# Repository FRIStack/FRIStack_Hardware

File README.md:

# FRI_STACK

Modular stackable embedded system based on ESP32 microcontrollers

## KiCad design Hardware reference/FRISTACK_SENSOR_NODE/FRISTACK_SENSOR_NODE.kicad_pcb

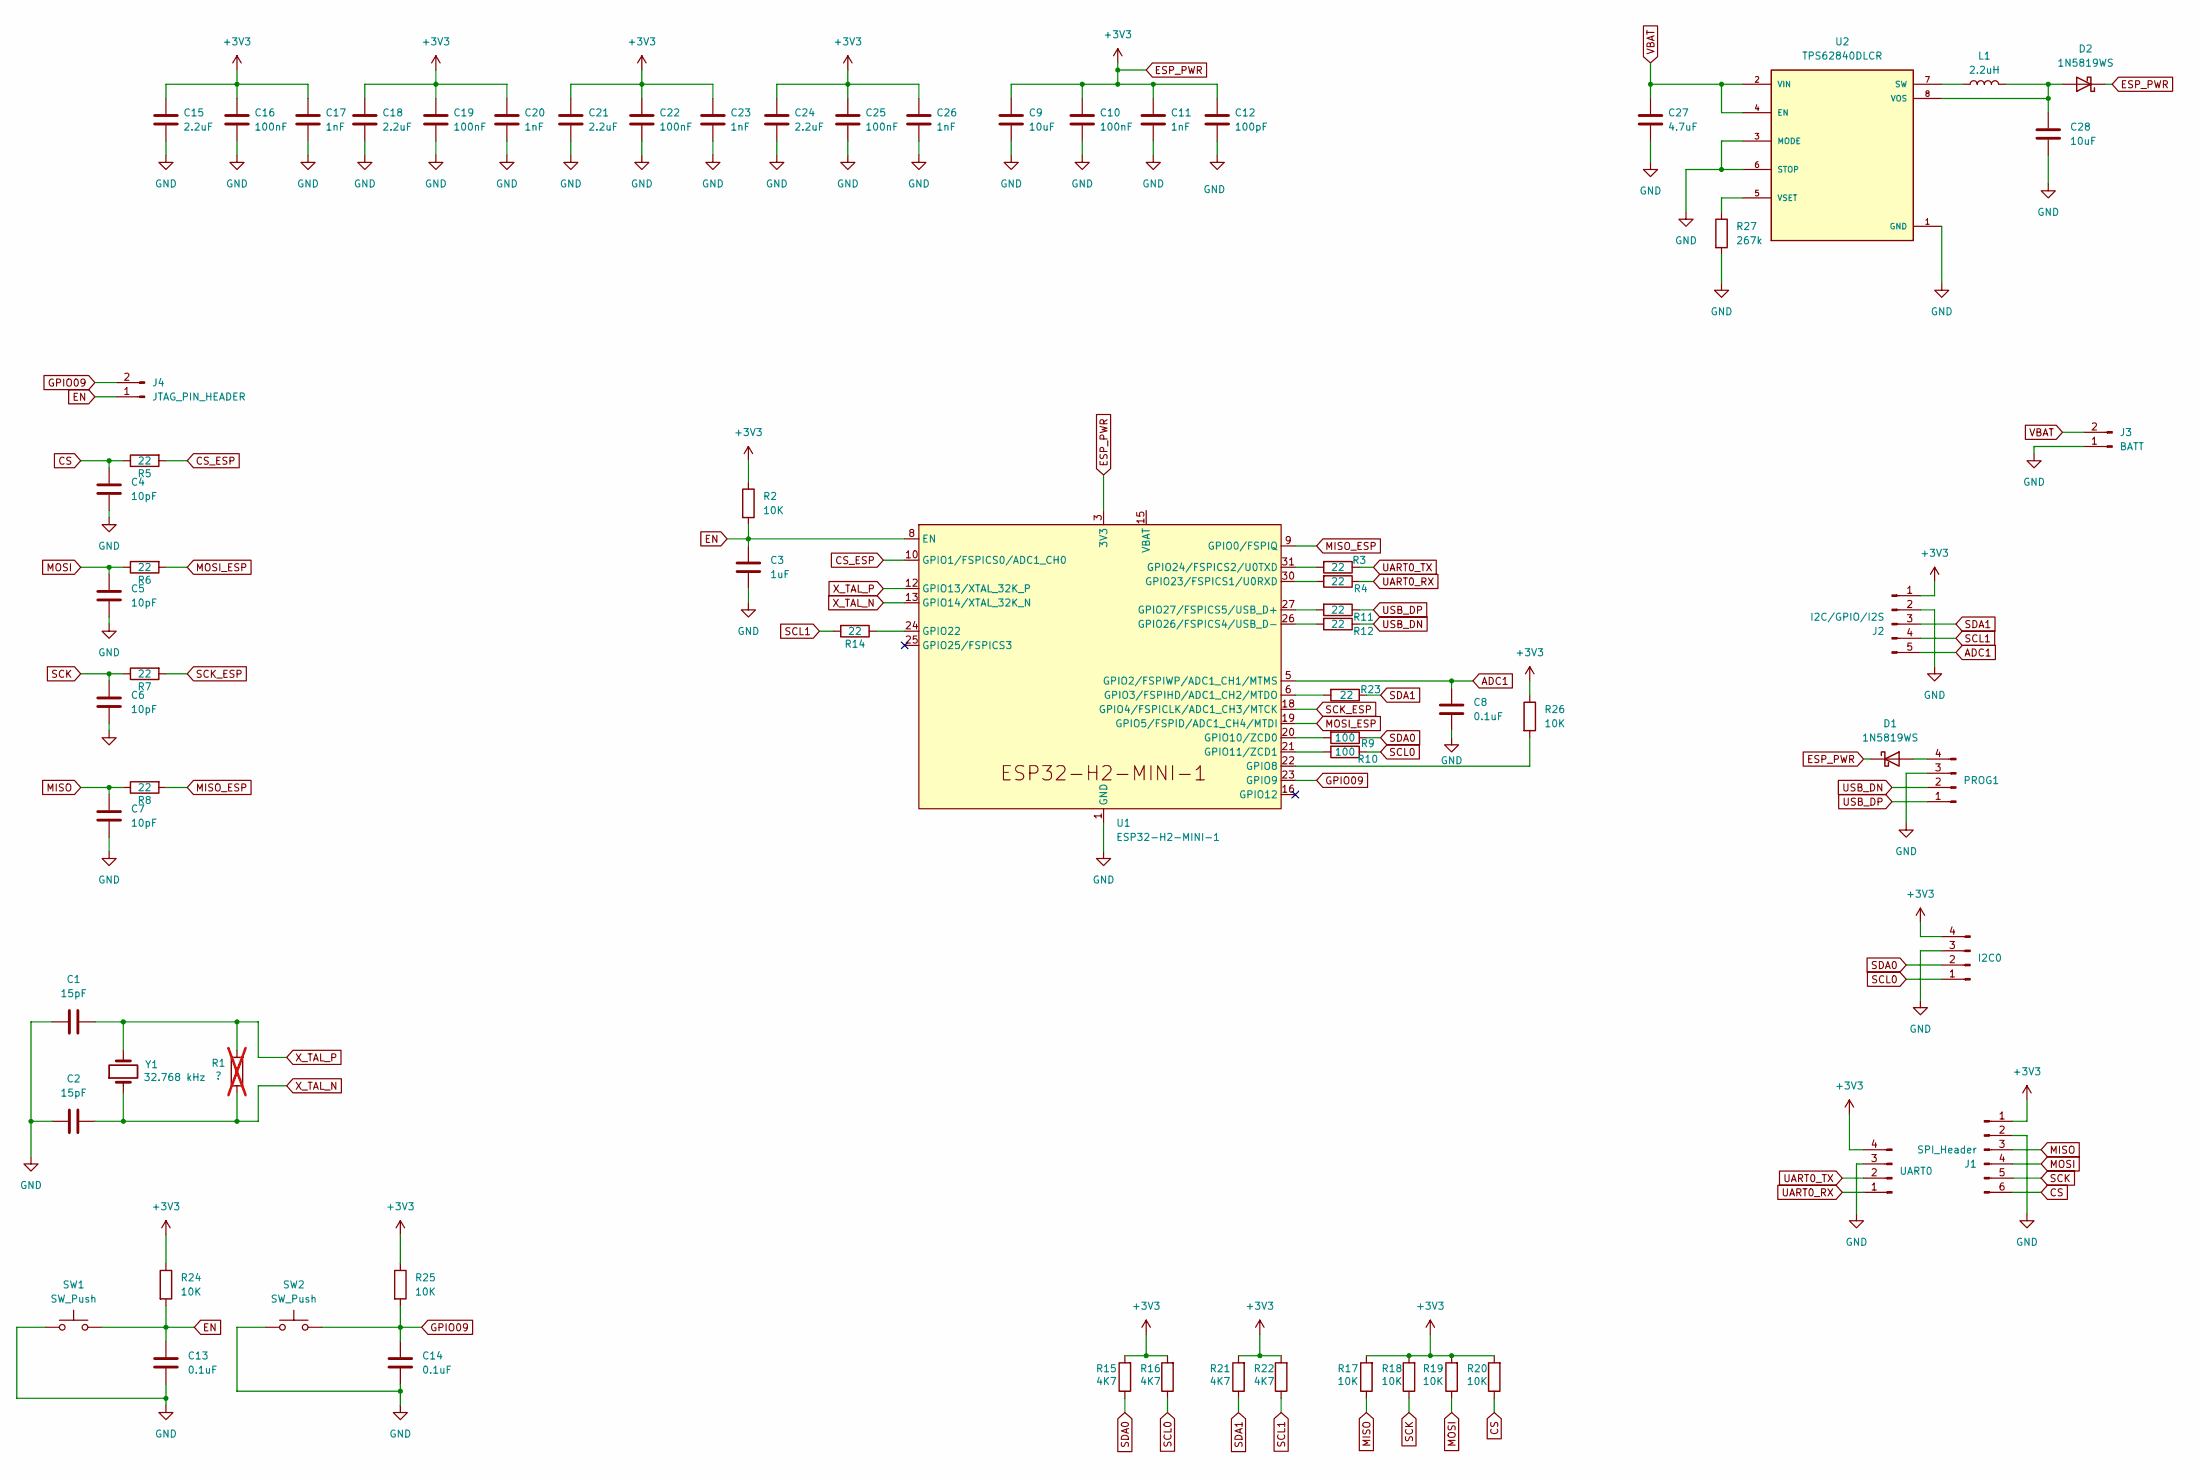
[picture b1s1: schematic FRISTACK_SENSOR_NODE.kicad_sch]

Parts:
C1, C2: 15pF; C_0603_1608Metric
C3: 1uF; C_0603_1608Metric
C4, C5, C6, C7: 10pF; C_0603_1608Metric
C8, C13, C14: 0.1uF; C_0603_1608Metric
C9: 10uF; C_0603_1608Metric
C10, C16, C19, C22, C25: 100nF; C_0603_1608Metric
C11, C17, C20, C23, C26: 1nF; C_0603_1608Metric
C12: 100pF; C_0603_1608Metric
C15, C18, C21, C24: 2.2uF; C_0603_1608Metric
C27: 4.7uF; C_0402_1005Metric
C28: 10uF; C_0402_1005Metric
D1, D2: 1N5819WS; D_SOD-323
I2C0: Conn_01x04_Pin; JST_PH_S4B-PH-K_1x04_P2.00mm_Horizontal
J1: SPI_Header; JST_PH_S6B-PH-K_1x06_P2.00mm_Horizontal
J2: I2C/GPIO/I2S; JST_PH_S5B-PH-K_1x05_P2.00mm_Horizontal
J3: BATT; JST_PH_S2B-PH-K_1x02_P2.00mm_Horizontal
J4: JTAG_PIN_HEADER; PinHeader_1x02_P2.54mm_Horizontal
L1: 2.2uH; INDC2016X120N
PROG1: Conn_01x04_Pin; JST_PH_S4B-PH-K_1x04_P2.00mm_Horizontal
R1: ?; R_0603_1608Metric; not fitted
R2, R17, R18, R19, R20, R24, R25, R26: 10K; R_0603_1608Metric
R3, R4, R5, R6, R7, R8, R11, R12, R14, R23: 22; R_0603_1608Metric
R9, R10: 100; R_0603_1608Metric
R15, R16, R21, R22: 4K7; R_0603_1608Metric
R27: 267k; R_0603_1608Metric
SW1, SW2: SW_Push; SW_TS-1088-AR02016
U1: ESP32-H2-MINI-1
U2: TPS62840DLCR; SON50P200X150X100-8N
UART0: Conn_01x04_Pin; JST_PH_S4B-PH-K_1x04_P2.00mm_Horizontal
Y1: 32.768 kHz; Crystal_SMD_G8-2Pin_3.2x1.5mm

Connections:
ADC1: C8.1, J2.5, U1.5 (GPIO2/FSPIWP/ADC1_CH1/MTMS)
CS: C4.1, J1.6, R5.1, R20.1
CS_ESP: R5.2, U1.10 (GPIO1/FSPICS0/ADC1_CH0)
EN: C3.1, C13.1, J4.1, R2.2, R24.2, SW1.2, U1.8 (EN); also elsewhere on the board
ESP_PWR: C9.1, C10.1, C11.1, C12.1, C15.1, C16.1, C17.1, C18.1, C19.1, C20.1, C21.1, C22.1, C23.1, C24.1, C25.1, C26.1, D1.1 (K), D2.1 (K), I2C0.4, J1.1, J2.1, R2.1, R15.2, R16.2, R17.2, R18.2, R19.2, R20.2, R21.2, R22.2, R24.1, R25.1, R26.1, U1.3 (3V3), UART0.4
GND: C1.1, C2.1, C3.2, C4.2, C5.2, C6.2, C7.2, C8.2, C9.2, C10.2, C11.2, C12.2, C13.2, C14.2, C15.2, C16.2, C17.2, C18.2, C19.2, C20.2, C21.2, C22.2, C23.2, C24.2, C25.2, C26.2, C27.2, C28.2, I2C0.3, J1.2, J2.2, J3.1, PROG1.3, R27.2, SW1.1, SW2.1, U1.1 (GND), U1.2 (GND), U1.11 (GND), U1.14 (GND), U1.36 (GND), U1.37 (GND), U1.38 (GND), U1.39 (GND), U1.40 (GND), U1.41 (GND), U1.42 (GND), U1.43 (GND), U1.44 (GND), U1.45 (GND), U1.46 (GND), U1.47 (GND), U1.48 (GND), U1.49 (GND), U1.50 (GND), U1.51 (GND), U1.52 (GND), U1.53 (GND), U2.1 (GND), U2.3 (MODE), U2.6 (STOP), UART0.3; also elsewhere on the board
GPIO09: C14.1, J4.2, R25.2, SW2.2, U1.23 (GPIO9); also elsewhere on the board
MISO: C7.1, J1.3, R8.1, R17.1
MISO_ESP: R8.2, U1.9 (GPIO0/FSPIQ)
MOSI: C5.1, J1.4, R6.1, R19.1
MOSI_ESP: R6.2, U1.19 (GPIO5/FSPID/ADC1_CH4/MTDI)
unnamed: D1.2 (A), PROG1.4
unnamed: C28.1, D2.2 (A), L1.2, U2.8 (VOS)
unnamed: R23.2, U1.6 (GPIO3/FSPIHD/ADC1_CH2/MTDO)
unnamed: R26.2, U1.22 (GPIO8)
unnamed: R9.2, U1.20 (GPIO10/ZCD0)
unnamed: R10.2, U1.21 (GPIO11/ZCD1)
unnamed: R14.1, U1.24 (GPIO22)
unnamed: R4.2, U1.30 (GPIO23/FSPICS1/U0RXD)
unnamed: R3.2, U1.31 (GPIO24/FSPICS2/U0TXD)
unnamed: R12.2, U1.26 (GPIO26/FSPICS4/USB_D-)
unnamed: R11.2, U1.27 (GPIO27/FSPICS5/USB_D+)
unnamed: L1.1, U2.7 (SW)
unnamed: R27.1, U2.5 (VSET)
SCK: C6.1, J1.5, R7.1, R18.1
SCK_ESP: R7.2, U1.18 (GPIO4/FSPICLK/ADC1_CH3/MTCK)
SCL0: I2C0.1, R10.1, R16.1
SCL1: J2.4, R14.2, R22.1
SDA0: I2C0.2, R9.1, R15.1
SDA1: J2.3, R21.1, R23.1
UART0_RX: R4.1, UART0.1
UART0_TX: R3.1, UART0.2
USB_DN: PROG1.2, R12.1
USB_DP: PROG1.1, R11.1
VBAT: C27.1, J3.2, U2.2 (VIN), U2.4 (EN)
X_TAL_N: C2.2, R1.1, U1.13 (GPIO14/XTAL_32K_N), Y1.1
X_TAL_P: C1.2, R1.2, U1.12 (GPIO13/XTAL_32K_P), Y1.2

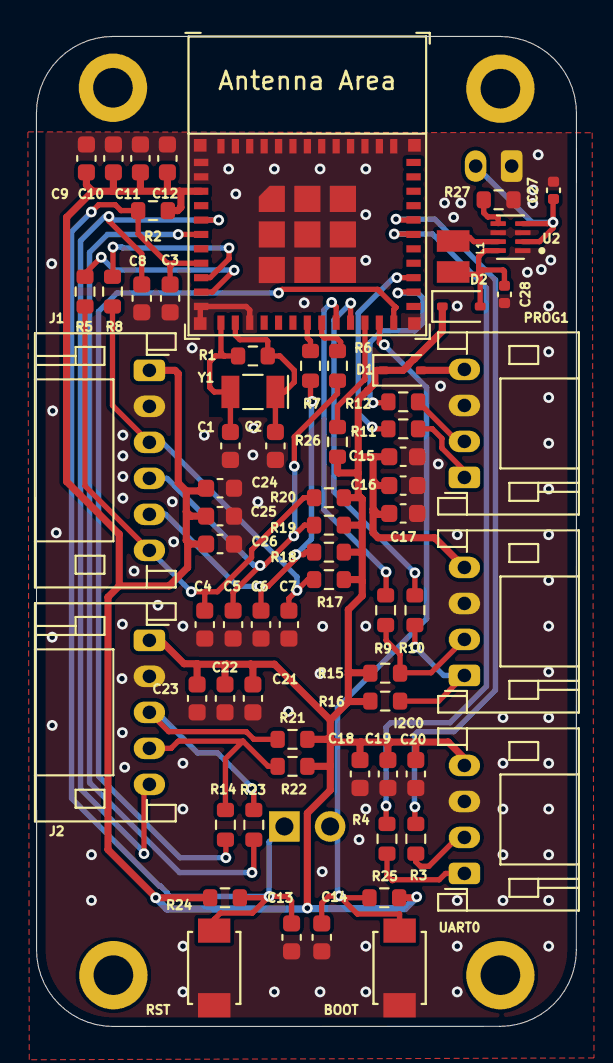
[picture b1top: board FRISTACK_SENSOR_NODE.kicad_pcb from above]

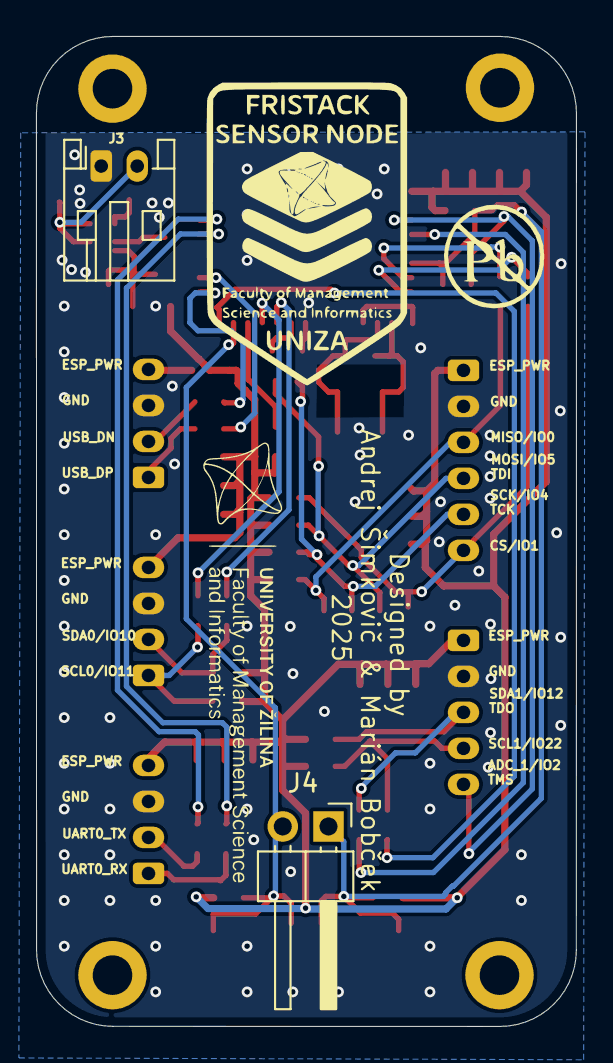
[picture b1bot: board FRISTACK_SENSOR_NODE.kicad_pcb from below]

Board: 2 copper layers, 30.0 x 55.0 mm, 69 parts (2 on the bottom side), 37 nets.

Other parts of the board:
BOOT: SW_Push; SW_TS-1088-AR02016
RST: SW_Push; SW_TS-1088-AR02016

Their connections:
EN: RST.2; also elsewhere on the board
GND: BOOT.1, RST.1; also elsewhere on the board
GPIO09: BOOT.2; also elsewhere on the board

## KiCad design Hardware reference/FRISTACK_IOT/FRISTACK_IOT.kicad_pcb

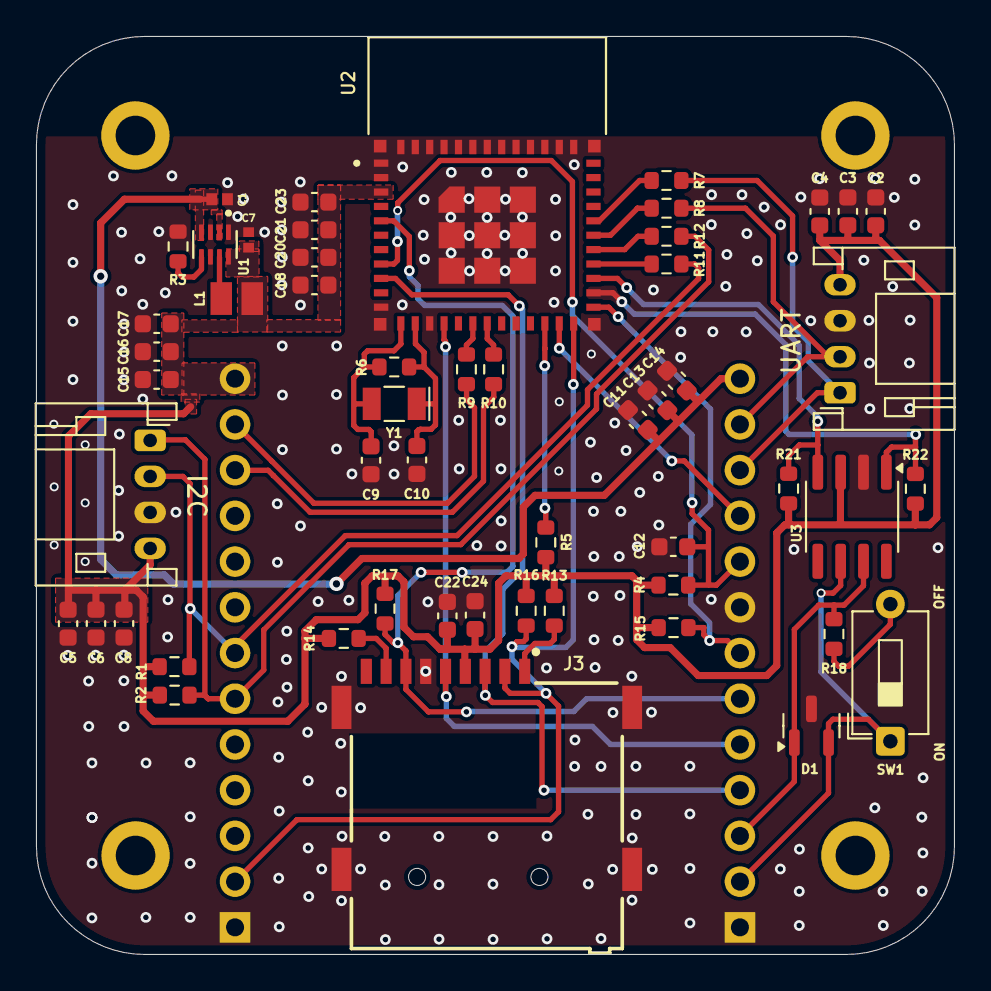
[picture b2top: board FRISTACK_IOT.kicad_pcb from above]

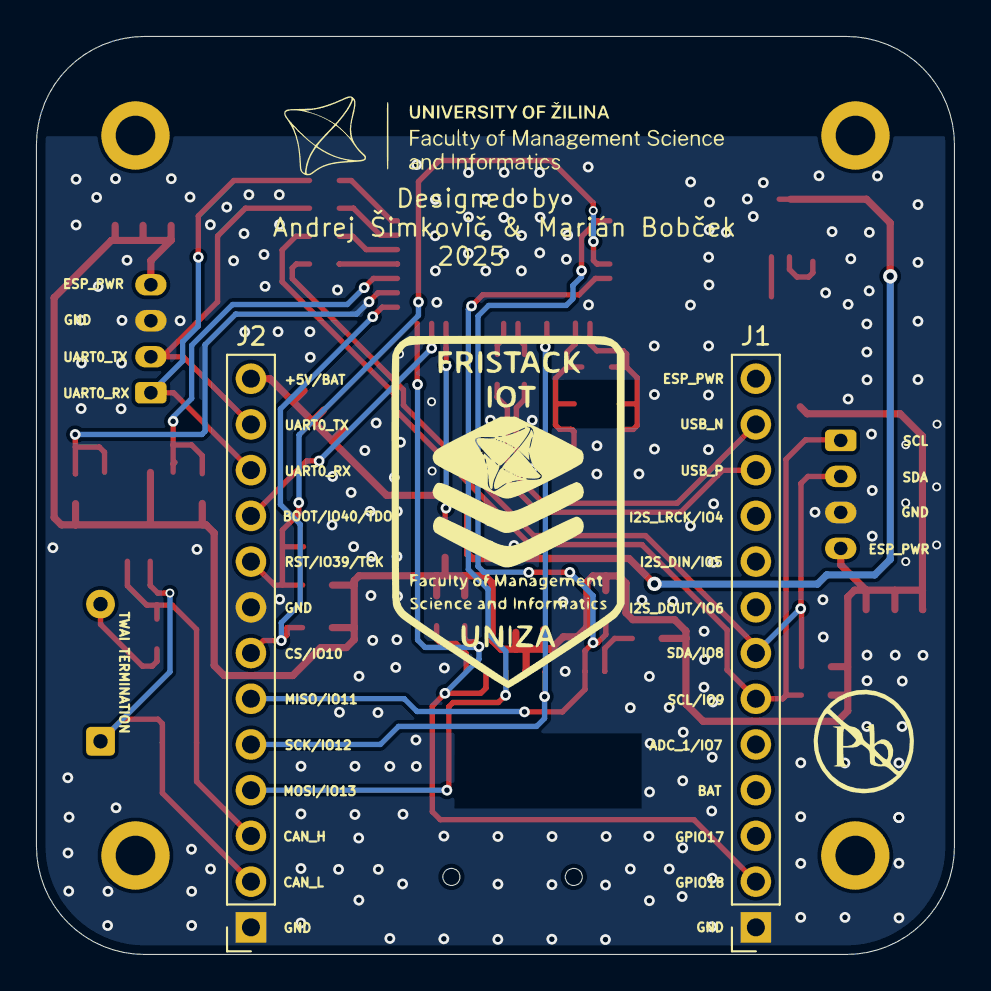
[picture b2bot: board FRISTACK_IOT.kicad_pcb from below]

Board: 2 copper layers, 51.0 x 51.0 mm, 55 parts (2 on the bottom side), 34 nets.

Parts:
C1: 4.7uF; CAPC1005X65N
C2, C5, C11, C15: 2.2uF; C_0603_1608Metric
C3, C6, C13, C16, C20, C24: 100nF; C_0603_1608Metric
C4, C8, C14, C17, C21: 1nF; C_0603_1608Metric
C7: 10uF; CAPC1005X55N
C9, C10: 15pF; C_0603_1608Metric
C12: 0.1uF; C_0603_1608Metric
C18: 22uF; C_0603_1608Metric
C22: 10uF; C_0603_1608Metric
C23: 100pF; C_0603_1608Metric
D1: PESD1CAN; SOT-23
I2C: Conn_01x04_Pin; JST_PH_S4B-PH-K_1x04_P2.00mm_Horizontal
J1, J2: Conn_01x13_Socket; PinSocket_1x13_P2.54mm_Vertical
J3: MEM2075-00-140-01-A; GCT_MEM2075-00-140-01-A
L1: 2.2uH; INDC2016X120N
R1, R2, R21, R22: 4K7; R_0603_1608Metric
R3: 267k; R_0603_1608Metric
R4, R5, R13, R14: 10K; R_0603_1608Metric
R6: ?; R_0603_1608Metric
R7, R8, R9, R10, R11, R12: 22; R_0603_1608Metric
R15, R16: 22K; R_0603_1608Metric
R17: 47K; R_0603_1608Metric
R18: 120; R_0603_1608Metric
SW1: SW_DIP_x01; SW_DIP_SPSTx01_Slide_6.7x4.1mm_W7.62mm_P2.54mm_LowProfile
U1: TPS62840DLCR; SON50P200X150X100-8N
U2: ESP32-C6-MINI-1-H4; XCVR_ESP32-C6-MINI-1-H4
U3: SN65HVD232; SOIC-8_3.9x4.9mm_P1.27mm
UART: Conn_01x04_Pin; JST_PH_S4B-PH-K_1x04_P2.00mm_Horizontal
Y1: 32.768 kHz; Crystal_SMD_G8-2Pin_3.2x1.5mm

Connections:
+5V: C1.1, C11.1, C13.1, C14.1, J2.13, U1.2 (VIN), U1.4 (EN)
CAN_D: R22.1, U2.26 (IO20), U3.1 (D)
CAN_H: D1.1 (K), J2.3, R18.1, U3.7 (CANH)
CAN_L: D1.2 (K), J2.2, SW1.1, U3.6 (CANL)
CAN_R: R21.2, U2.27 (IO21), U3.4 (R)
CS: J2.7, R15.1, U2.25 (IO19)
ESP_PWR: C2.1, C3.1, C4.1, C5.1, C6.1, C7.1, C8.1, C15.1, C16.1, C17.1, C18.1, C20.1, C21.1, C22.1, C23.1, C24.1, I2C.4, J1.13, J3.P4 (VDD), L1.2, R1.2, R2.2, R4.1, R5.2, R13.2, R14.2, R15.2, R16.2, R17.2, R21.1, R22.2, U1.8 (VOS), U2.3 (3V3), U3.3 (VCC), UART.4
FLASH_BOOT: J2.10, U2.23 (IO9)
FLASH_RST: C12.1, J2.9, R4.2, U2.8 (EN)
GND: C1.2, C2.2, C3.2, C4.2, C5.2, C6.2, C7.2, C8.2, C9.1, C10.1, C11.2, C12.2, C13.2, C14.2, C15.2, C16.2, C17.2, C18.2, C20.2, C21.2, C22.2, C23.2, C24.2, D1.3 (A), I2C.3, J1.1, J2.1, J2.8, J3.P6 (VSS), J3.SH1 (SHIELD), J3.SH2 (SHIELD), J3.SH3 (SHIELD), J3.SH4 (SHIELD), R3.2, U1.1 (GND), U1.3 (MODE), U1.6 (STOP), U2.1 (GND1), U2.2 (GND1), U2.11 (GND1), U2.14 (GND1), U2.36 (GND1), U2.37 (GND1), U2.38 (GND1), U2.39 (GND1), U2.40 (GND1), U2.41 (GND1), U2.42 (GND1), U2.43 (GND1), U2.44 (GND1), U2.45 (GND1), U2.46 (GND1), U2.47 (GND2), U2.48 (GND2), U2.49_1 (GND2), U2.49_2 (GND2), U2.49_3 (GND2), U2.49_4 (GND2), U2.49_5 (GND2), U2.49_6 (GND2), U2.49_7 (GND2), U2.49_8 (GND2), U2.49_9 (GND2), U2.50 (GND2), U2.51 (GND2), U2.52 (GND2), U2.53 (GND2), U3.2 (GND), UART.3
MISO: J2.6, J3.P7 (DAT0), R17.1, U2.5 (IO2)
MOSI: J2.4, J3.P3 (CMD), U2.9 (IO4)
unnamed: R18.2, SW1.2
unnamed: L1.1, U1.7 (SW)
unnamed: R3.1, U1.5 (VSET)
unnamed: R5.1, U2.22 (IO8)
unnamed: R9.2, U2.17 (IO12)
unnamed: R10.2, U2.18 (IO13)
unnamed: R11.2, U2.28 (IO22)
unnamed: R12.2, U2.29 (IO23)
unnamed: R8.2, U2.30 (RXD0)
unnamed: R7.2, U2.31 (TXD0)
SCK: J2.5, J3.P5 (CLK), U2.15 (IO6)
SCL: I2C.1, J1.6, R2.1, R12.1
SDA: I2C.2, J1.7, R1.1, R11.1
SD_CS: J1.2, J3.P2 (CD/DAT3), R16.1, U2.24 (IO18)
SD_DAT_1: J3.P8 (DAT1), R14.1
SD_DAT_2: J3.P1 (DAT2), R13.1
UART0_RX: J2.12, R8.1, UART.2
UART0_TX: J2.11, R7.1, UART.1
USB_N_HD: J1.12, R9.1
USB_P_HD: J1.11, R10.1
XTAL_32K_N: C10.2, R6.1, U2.13 (IO1), Y1.1
XTAL_32K_P: C9.2, R6.2, U2.12 (IO0), Y1.2

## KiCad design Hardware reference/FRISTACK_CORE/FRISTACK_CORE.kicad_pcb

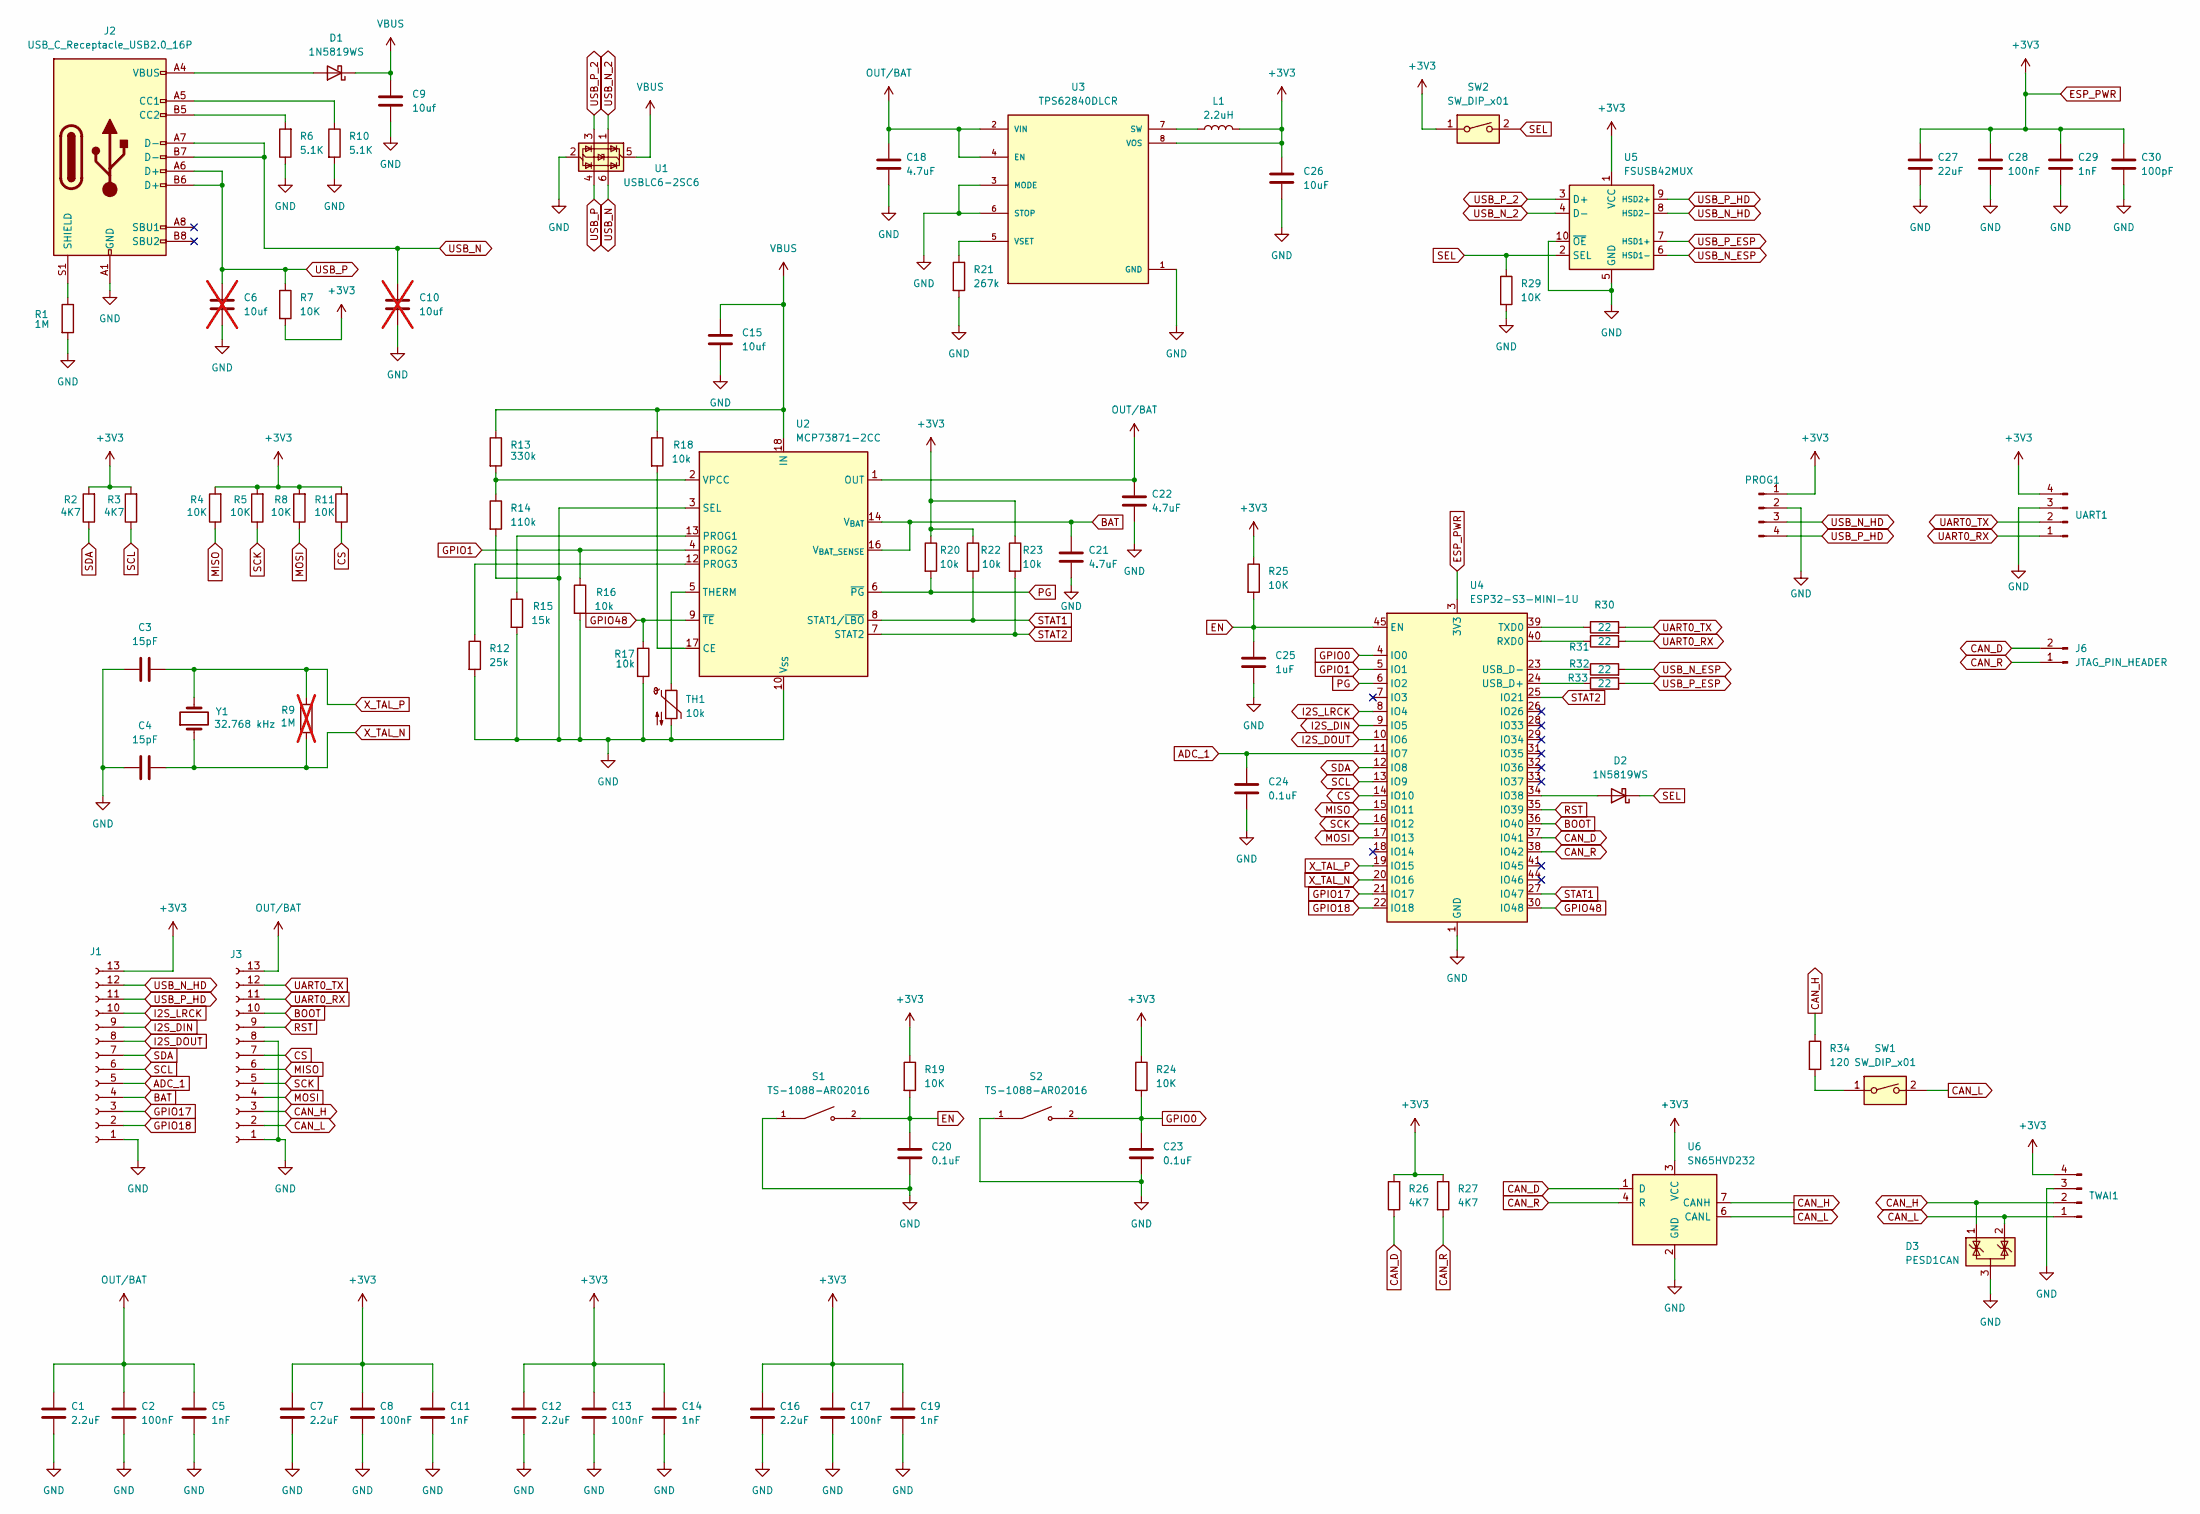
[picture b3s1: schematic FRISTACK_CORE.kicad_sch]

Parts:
C1, C7, C12, C16: 2.2uF; C_0402_1005Metric
C2, C8, C13, C17, C28: 100nF; C_0402_1005Metric
C3, C4: 15pF; C_0402_1005Metric
C5, C11, C14, C19, C29: 1nF; C_0402_1005Metric
C6, C10: 10uf; C_0402_1005Metric; not fitted
C9, C15: 10uf; C_0402_1005Metric
C18, C21, C22: 4.7uF; C_0402_1005Metric
C20, C23, C24: 0.1uF; C_0402_1005Metric
C25: 1uF; C_0402_1005Metric
C26: 10uF; C_0402_1005Metric
C27: 22uF; C_0603_1608Metric
C30: 100pF; C_0402_1005Metric
D1, D2: 1N5819WS; D_SOD-323
D3: PESD1CAN; SOT-23
J1, J3: Conn_01x13_Socket; PinSocket_1x13_P2.54mm_Vertical
J2: USB_C_Receptacle_USB2.0_16P; USB_C_Receptacle_GCT_USB4105-xx-A_16P_TopMnt_Horizontal
J6: JTAG_PIN_HEADER; PinHeader_1x02_P2.54mm_Horizontal
L1: 2.2uH; INDC2016X120N
PROG1: Conn_01x04_Pin; JST_PH_S4B-PH-K_1x04_P2.00mm_Horizontal
R1: 1M; R_0402_1005Metric
R2, R3, R26, R27: 4K7; R_0402_1005Metric
R4, R5, R7, R8, R11, R19, R24, R25, R29: 10K; R_0402_1005Metric
R6, R10: 5.1K; R_0402_1005Metric
R9: 1M; R_0402_1005Metric; not fitted
R12: 25k; R_0402_1005Metric
R13: 330k; R_0402_1005Metric
R14: 110k; R_0402_1005Metric
R15: 15k; R_0402_1005Metric
R16, R17, R18, R20, R22, R23: 10k; R_0402_1005Metric
R21: 267k; R_0402_1005Metric
R30, R31, R32, R33: 22; R_0402_1005Metric
R34: 120; R_0402_1005Metric
S1, S2: TS-1088-AR02016; SW_TS-1088-AR02016; PARTREV N/A
SW1, SW2: SW_DIP_x01; SW_DIP_SPSTx01_Slide_6.7x4.1mm_W7.62mm_P2.54mm_LowProfile
TH1: 10k; R_0603_1608Metric
TWAI1: Conn_01x04_Pin; JST_PH_S4B-PH-K_1x04_P2.00mm_Horizontal
U1: USBLC6-2SC6; SOT-23-6
U2: MCP73871-2CC; QFN-20-1EP_4x4mm_P0.5mm_EP2.5x2.5mm
U3: TPS62840DLCR; SON50P200X150X100-8N
U4: ESP32-S3-MINI-1U
U5: FSUSB42MUX; MSOP-10_3x3mm_P0.5mm
U6: SN65HVD232; SOIC-8_3.9x4.9mm_P1.27mm
UART1: Conn_01x04_Pin; JST_PH_S4B-PH-K_1x04_P2.00mm_Horizontal
Y1: 32.768 kHz; Crystal_SMD_G8-2Pin_3.2x1.5mm

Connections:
ADC_1: C24.1, J1.5, U4.11 (IO7)
BAT: C21.1, J1.4, U2.14 (V_{BAT}), U2.15 (V_{BAT}), U2.16 (V_{BAT_SENSE})
BOOT: J3.10, U4.36 (IO40)
CAN_D: J6.2, R26.1, U4.37 (IO41), U6.1 (D)
CAN_H: D3.1 (K), J3.3, R34.1, TWAI1.2, U6.7 (CANH)
CAN_L: D3.2 (K), J3.2, SW1.2, TWAI1.1, U6.6 (CANL)
CAN_R: J6.1, R27.2, U4.38 (IO42), U6.4 (R)
CS: J3.7, R11.1, U4.14 (IO10)
EN: C20.1, C25.1, R19.2, R25.2, S1.2, U4.45 (EN); also elsewhere on the board
ESP_PWR: C7.1, C8.1, C11.1, C12.1, C13.1, C14.1, C16.1, C17.1, C19.1, C26.1, C27.1, C28.1, C29.1, C30.1, J1.13, L1.2, PROG1.1, R2.2, R3.2, R4.2, R5.2, R7.2, R8.2, R11.2, R19.1, R20.1, R22.1, R23.1, R24.1, R25.1, R26.2, R27.1, SW2.1, TWAI1.4, U3.8 (VOS), U4.3 (3V3), U5.1 (VCC), U6.3 (VCC), UART1.4
GND: C1.2, C2.2, C3.1, C4.1, C5.2, C6.2, C7.2, C8.2, C9.2, C10.2, C11.2, C12.2, C13.2, C14.2, C15.2, C16.2, C17.2, C18.2, C19.2, C20.2, C21.2, C22.2, C23.2, C24.2, C25.2, C26.2, C27.2, C28.2, C29.2, C30.2, D3.3 (A), J1.1, J2.A1 (GND), J2.A12 (GND), J2.B1 (GND), J2.B12 (GND), J3.1, J3.8, PROG1.2, R1.2, R6.1, R10.2, R12.2, R14.2, R15.2, R16.2, R17.2, R21.2, R29.2, S1.1, S2.1, TH1.2, TWAI1.3, U1.2 (GND), U2.3 (SEL), U2.10 (V_{SS}), U2.11 (V_{SS}), U2.21 (V_{SS}), U3.1 (GND), U3.3 (MODE), U3.6 (STOP), U4.1 (GND), U4.2 (GND), U4.42 (GND), U4.43 (GND), U4.46 (GND), U4.47 (GND), U4.48 (GND), U4.49 (GND), U4.50 (GND), U4.51 (GND), U4.52 (GND), U4.53 (GND), U4.54 (GND), U4.55 (GND), U4.56 (GND), U4.57 (GND), U4.58 (GND), U4.59 (GND), U4.60 (GND), U4.61 (GND), U4.62 (GND), U4.63 (GND), U4.64 (GND), U4.65 (GND), U5.5 (GND), U5.10 (~OE), U6.2 (GND), UART1.3; also elsewhere on the board
GPIO0: C23.1, R24.2, S2.2, U4.4 (IO0); also elsewhere on the board
GPIO1: R16.1, U2.4 (PROG2), U4.5 (IO1)
GPIO17: J1.3, U4.21 (IO17)
GPIO18: J1.2, U4.22 (IO18)
GPIO48: R17.1, U2.9 (~TE), U4.30 (IO48)
I2S_DIN: J1.9, U4.9 (IO5)
I2S_DOUT: J1.8, U4.10 (IO6)
I2S_LRCK: J1.10, U4.8 (IO4)
MISO: J3.6, R4.1, U4.15 (IO11)
MOSI: J3.4, R8.1, U4.17 (IO13)
unnamed: D1.2 (A), J2.A4 (VBUS), J2.A9 (VBUS), J2.B4 (VBUS), J2.B9 (VBUS)
unnamed: D2.2 (A), U4.34 (IO38)
unnamed: J2.A5 (CC1), R10.1
unnamed: J2.B5 (CC2), R6.2
unnamed: J2.S1 (SHIELD), R1.1
unnamed: R34.2, SW1.1
unnamed: R18.2, U2.17 (CE)
unnamed: R15.1, U2.13 (PROG1)
unnamed: R12.1, U2.12 (PROG3)
unnamed: TH1.1, U2.5 (THERM)
unnamed: R13.2, R14.1, U2.2 (VPCC)
unnamed: L1.1, U3.7 (SW)
unnamed: R21.1, U3.5 (VSET)
unnamed: R31.1, U4.40 (RXD0)
unnamed: R30.1, U4.39 (TXD0)
unnamed: R33.1, U4.24 (USB_D+)
unnamed: R32.1, U4.23 (USB_D-)
OUT/BAT: C1.1, C2.1, C5.1, C18.1, C22.1, J3.13, U2.1 (OUT), U2.20 (OUT), U3.2 (VIN), U3.4 (EN)
PG: R20.2, U2.6 (~PG), U4.6 (IO2)
RST: J3.9, U4.35 (IO39)
SCK: J3.5, R5.1, U4.16 (IO12)
SCL: J1.6, R3.1, U4.13 (IO9)
SDA: J1.7, R2.1, U4.12 (IO8)
SEL: D2.1 (K), R29.1, SW2.2, U5.2 (SEL)
STAT1: R22.2, U2.8 (STAT1/~LBO), U4.27 (IO47)
STAT2: R23.2, U2.7 (STAT2), U4.25 (IO21)
UART0_RX: J3.11, R31.2, UART1.1
UART0_TX: J3.12, R30.2, UART1.2
USB_N: C10.1, J2.A7 (D-), J2.B7 (D-), U1.6 (I/O1)
USB_N_2: U1.1 (I/O1), U5.4 (D-)
USB_N_ESP: R32.2, U5.6 (HSD1-)
USB_N_HD: J1.12, PROG1.3, U5.8 (HSD2-)
USB_P: C6.1, J2.A6 (D+), J2.B6 (D+), R7.1, U1.4 (I/O2)
USB_P_2: U1.3 (I/O2), U5.3 (D+)
USB_P_ESP: R33.2, U5.7 (HSD1+)
USB_P_HD: J1.11, PROG1.4, U5.9 (HSD2+)
VBUS: C9.1, C15.1, D1.1 (K), R13.1, R18.1, U1.5 (VBUS), U2.18 (IN), U2.19 (IN)
X_TAL_N: C4.2, R9.1, U4.20 (IO16), Y1.1
X_TAL_P: C3.2, R9.2, U4.19 (IO15), Y1.2

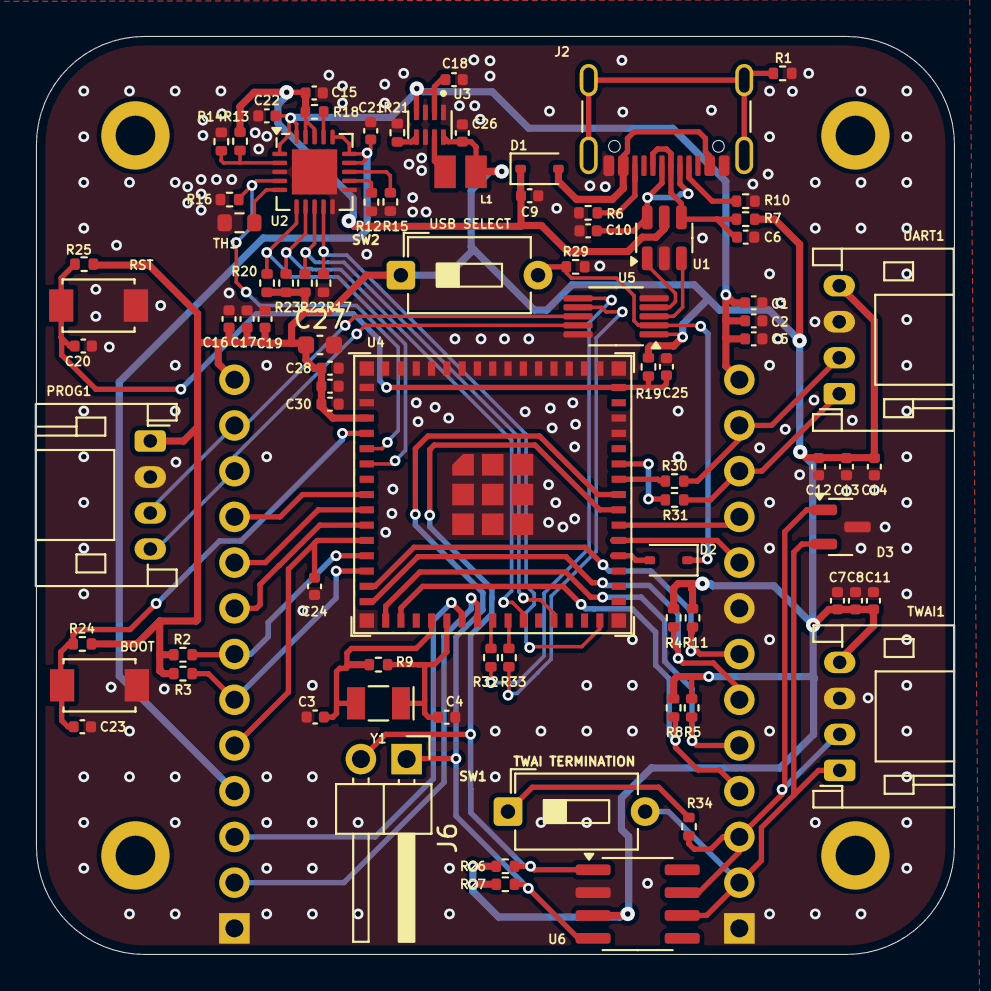
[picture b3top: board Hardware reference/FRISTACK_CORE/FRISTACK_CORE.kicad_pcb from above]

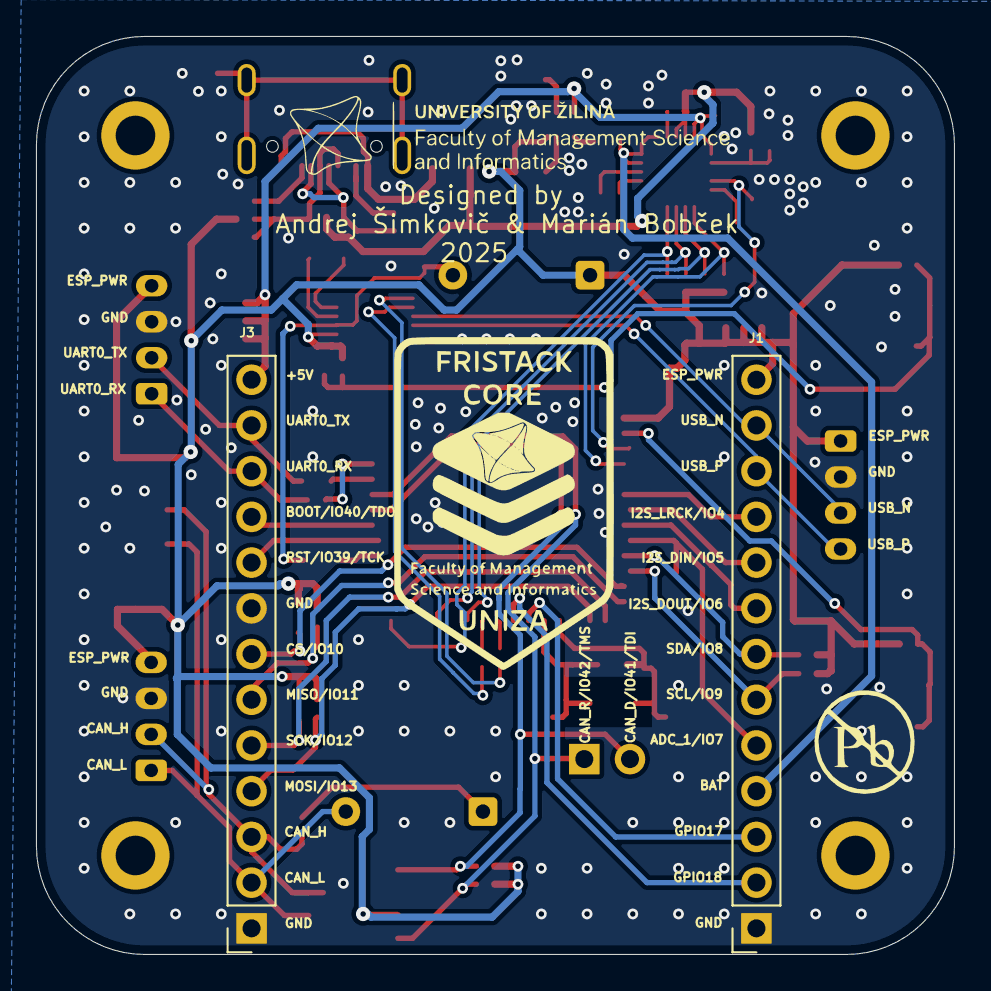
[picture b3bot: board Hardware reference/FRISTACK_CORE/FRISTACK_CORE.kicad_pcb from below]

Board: 2 copper layers, 51.0 x 51.0 mm, 86 parts (2 on the bottom side), 60 nets.

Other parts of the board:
BOOT: TS-1088-AR02016; SW_TS-1088-AR02016
RST: TS-1088-AR02016; SW_TS-1088-AR02016

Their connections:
EN: RST.2; also elsewhere on the board
GND: BOOT.1, RST.1; also elsewhere on the board
GPIO0: BOOT.2; also elsewhere on the board

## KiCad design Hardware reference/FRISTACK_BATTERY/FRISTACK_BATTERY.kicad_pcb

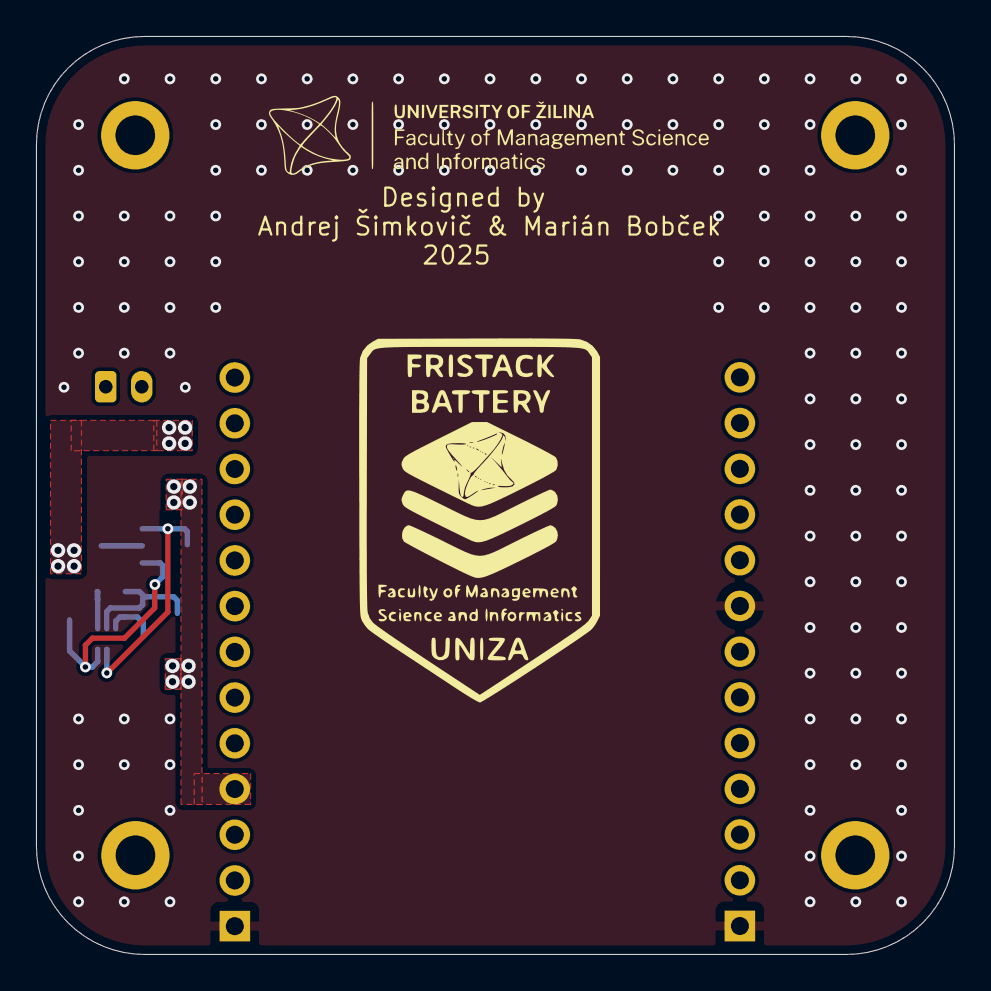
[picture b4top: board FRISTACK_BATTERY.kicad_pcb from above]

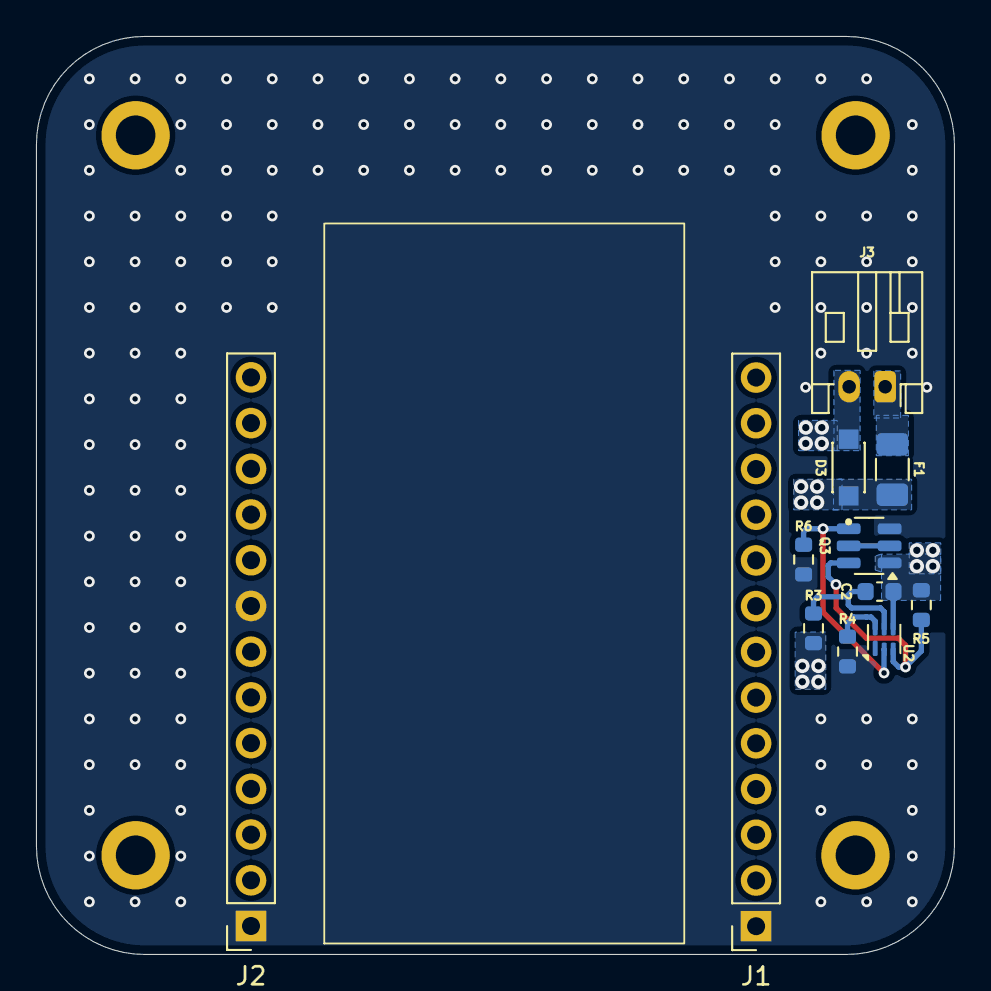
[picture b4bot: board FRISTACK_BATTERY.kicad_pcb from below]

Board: 2 copper layers, 51.0 x 51.0 mm, 12 parts (12 on the bottom side), 9 nets.

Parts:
C2: 0.1uF; C_0603_1608Metric
D3: SMF5.0A; SODFL3718X102N
F1: 1206L150TH1; Fuse_1206_3216Metric
J1, J2: Conn_01x13_Socket; PinSocket_1x13_P2.54mm_Vertical
J3: BAT; JST_PH_S2B-PH-K_1x02_P2.00mm_Horizontal
Q3: DMG9926UDM; SOT-23-6
R3: 330; R_0603_1608Metric
R4: 2.2k; R_0603_1608Metric
R5, R6: 5M; R_0603_1608Metric
U2: BQ29700DSER; WSON-6_1.5x1.5mm_P0.5mm

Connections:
BAT: D3.C, F1.1, J1.4, R3.1
CELL-: C2.2, D3.A, J3.2, Q3.1 (D1), R5.2, U2.4 (VSS)
unnamed: F1.2, J3.1
unnamed: Q3.6 (G1), R5.1, U2.3 (Dout)
unnamed: Q3.4 (G2), R6.1, U2.2 (Cout)
unnamed: Q3.2 (S1/D2), Q3.5 (S1/D2)
unnamed: C2.1, R3.2, U2.5 (BAT)
unnamed: R4.1, U2.6 (V-)
PACK-: J1.1, J2.1, J2.8, Q3.3 (S2), R4.2, R6.2
